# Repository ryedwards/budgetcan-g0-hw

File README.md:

# BUDGETCANFD_G0-Hardware
 BUDGETCANFD_G0-Hardware files

# HARDWARE IMAGE

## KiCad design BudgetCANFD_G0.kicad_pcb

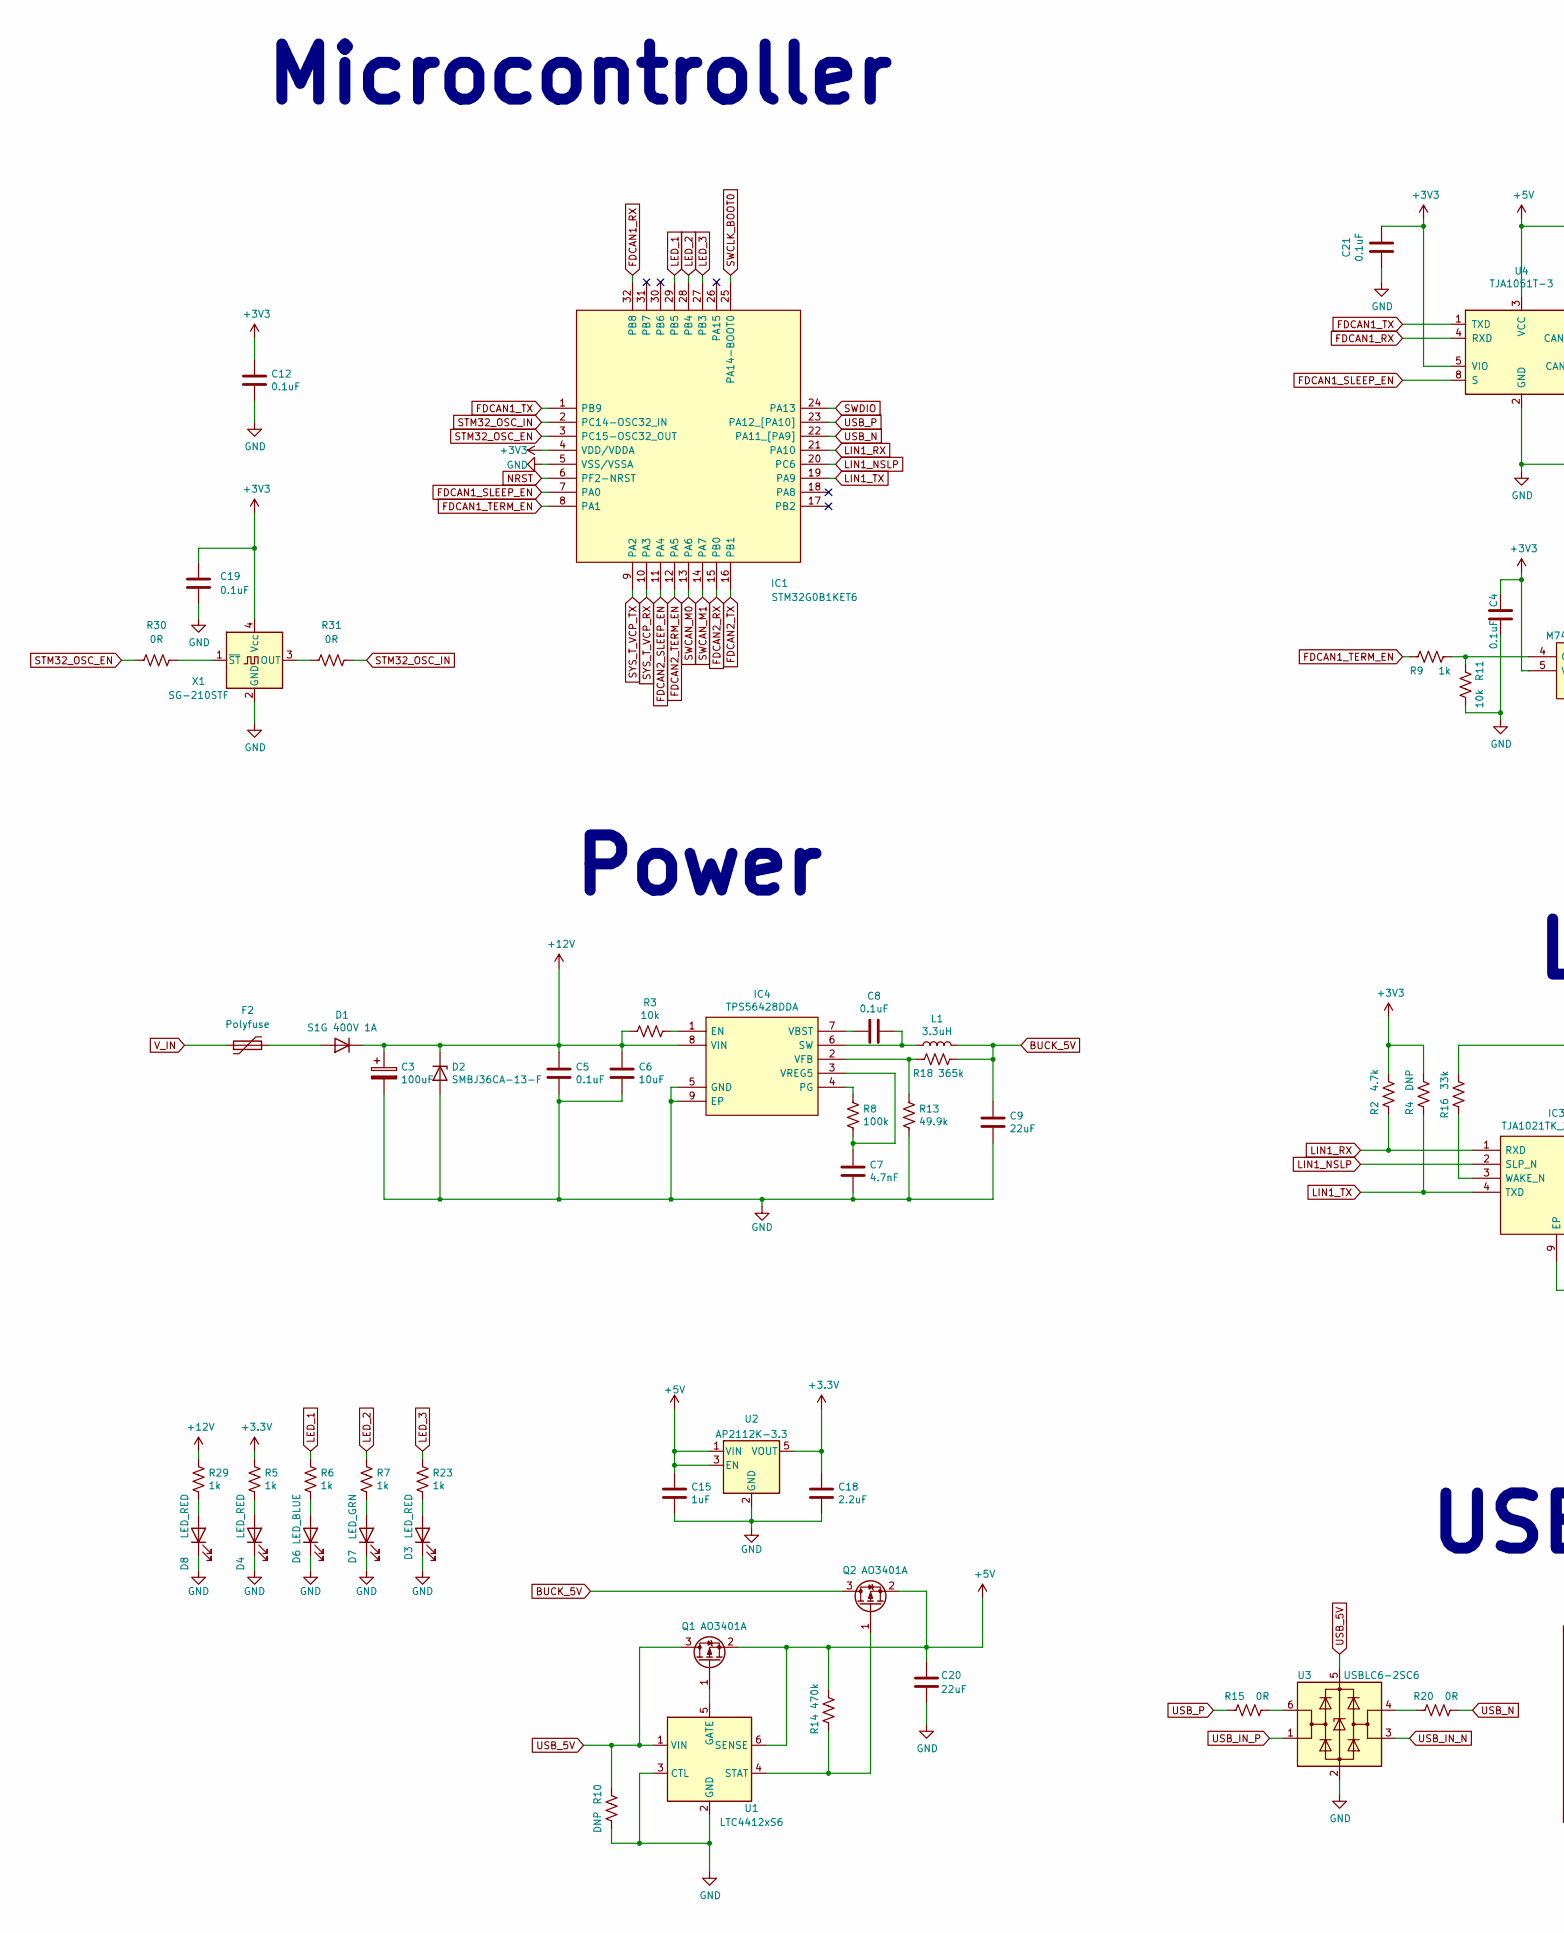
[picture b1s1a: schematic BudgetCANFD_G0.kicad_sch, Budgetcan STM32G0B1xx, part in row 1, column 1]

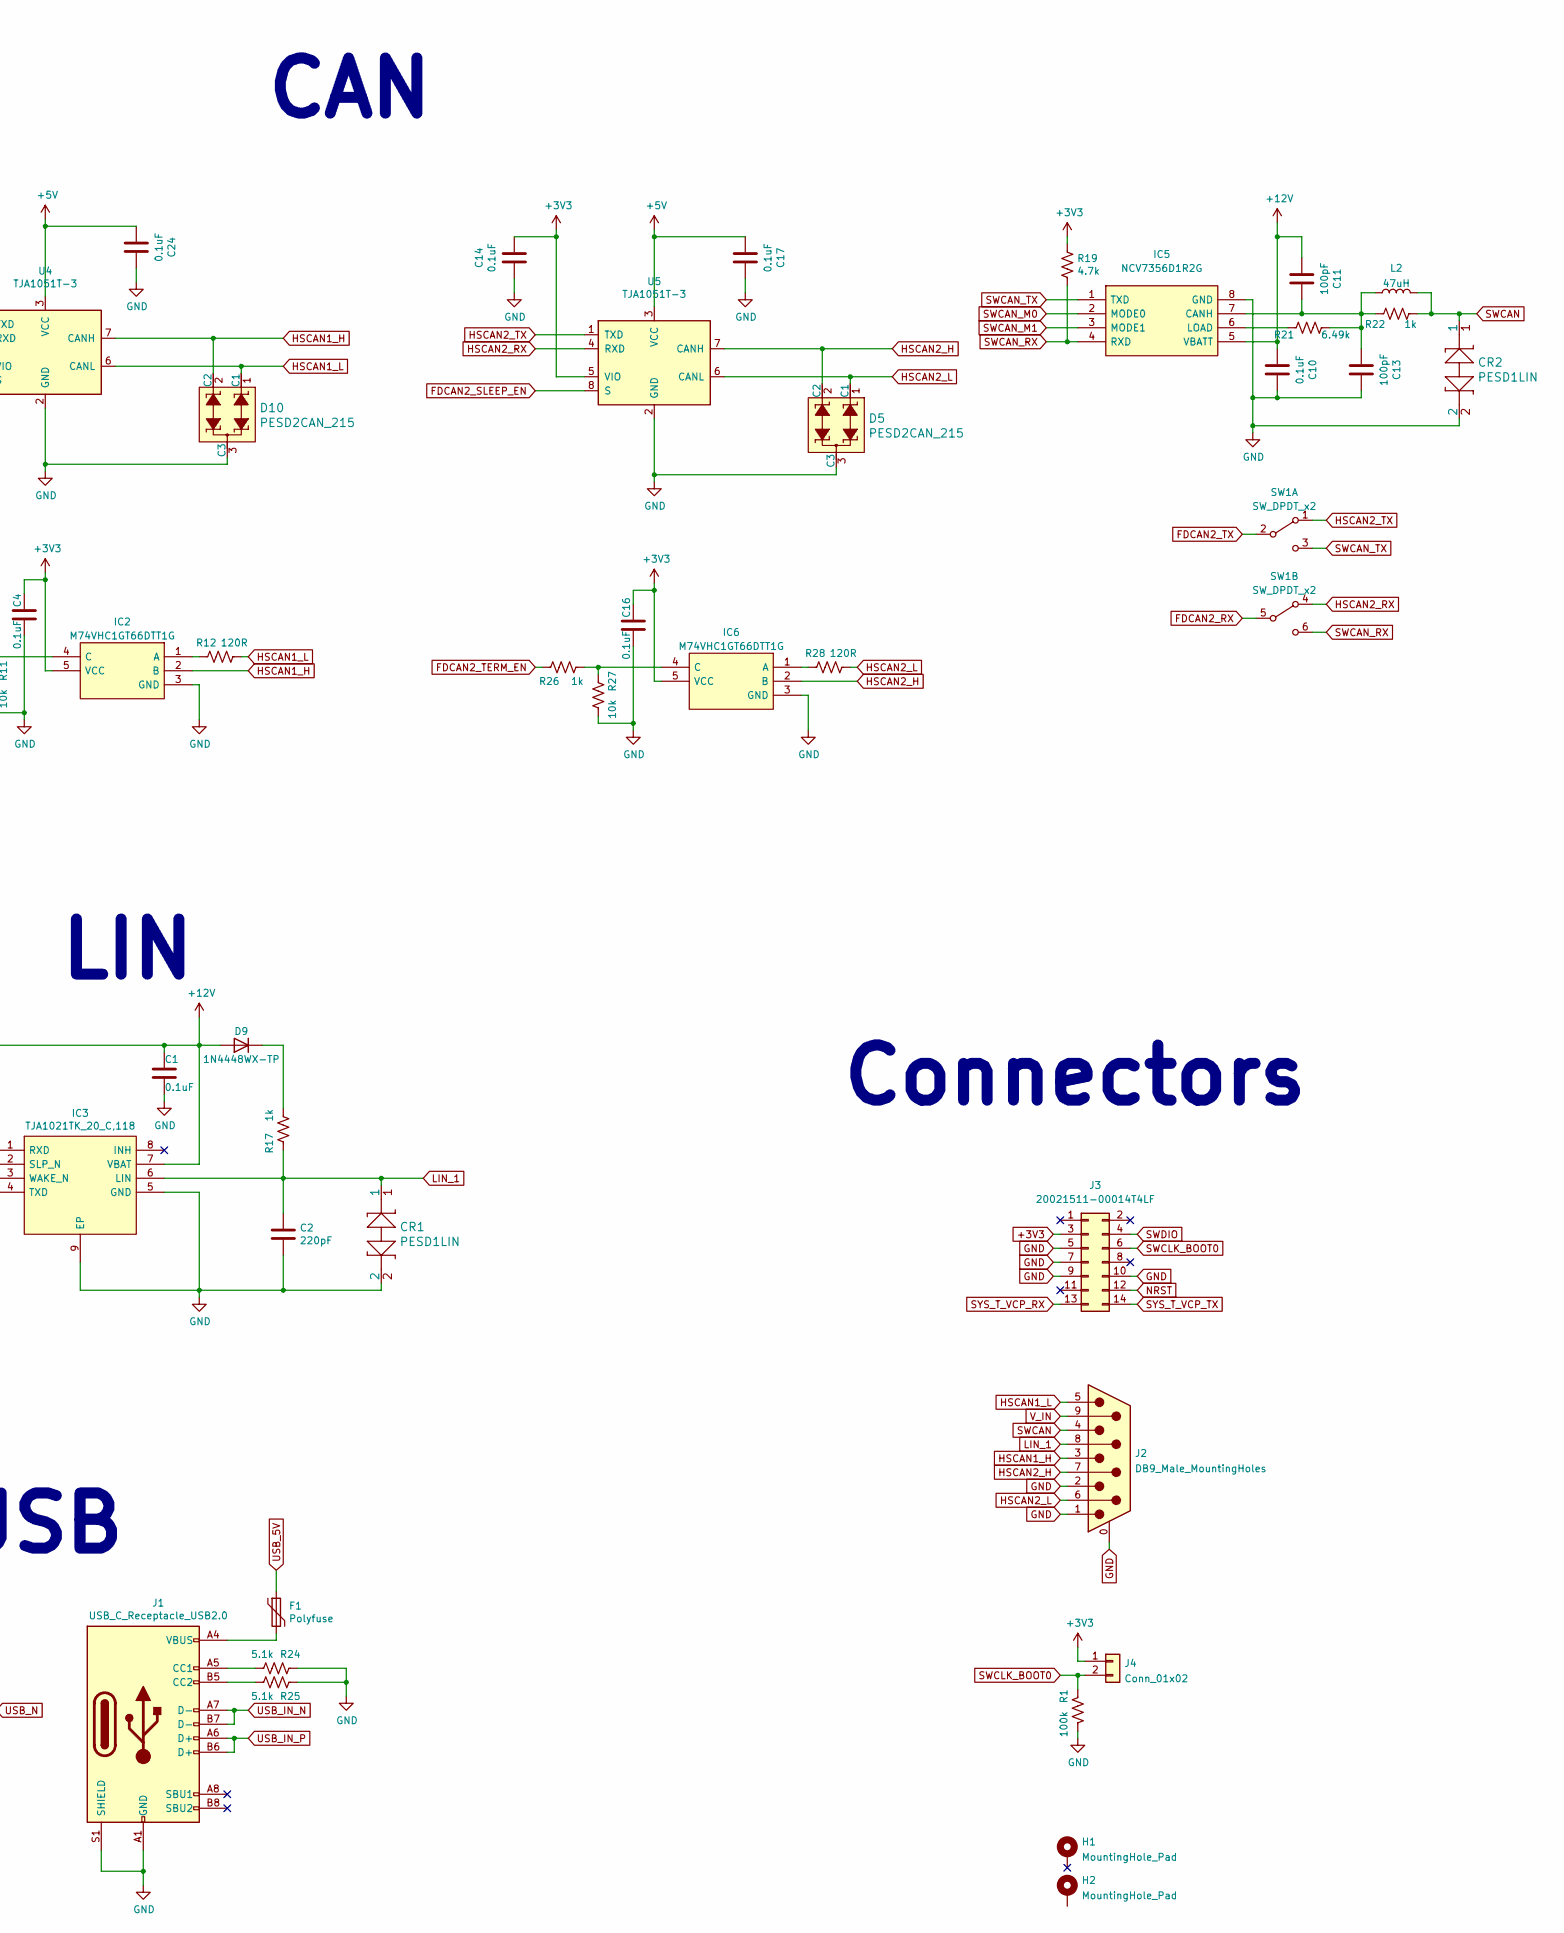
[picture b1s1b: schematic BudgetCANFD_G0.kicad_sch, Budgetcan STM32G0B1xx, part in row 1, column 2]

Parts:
C1, C4, C5, C8, C10, C12, C14, C16, C17, C21, C24: 0.1uF; C_0603_1608Metric; Manufacturer_Part_Number CC0603KRX7R8BB104; LCSC Part # C14663
C2: 220pF; C_0603_1608Metric; Manufacturer_Part_Number CC0603JRNPO9BN221; LCSC Part # C1603
C3: 100uF; CP_Elec_6.3x7.7; Manufacturer_Part_Number EMZA250ADA101MF80G; LCSC Part # C127971
C6: 10uF; C_1206_3216Metric; Manufacturer_Part_Number CL31B106KQHNFNE; LCSC Part # C13585
C7: 4.7nF; C_0603_1608Metric; Manufacturer_Part_Number CGA3E2X7R2A472K080AA; LCSC Part # C53987
C9, C20: 22uF; C_1206_3216Metric; Manufacturer_Part_Number EMK316ABJ226ML-T; LCSC Part # C90146
C11, C13: 100pF; C_0805_2012Metric; Manufacturer_Part_Number CC0603KRX7R8BB104; LCSC Part # C14663
C15: 1uF; C_0603_1608Metric; Manufacturer_Part_Number CC0603KRX7R8BB104; LCSC Part # C14663
C18: 2.2uF; C_0603_1608Metric; Manufacturer_Part_Number CC0603KRX7R8BB104; LCSC Part # C14663
C19: 0.1uF; C_0402_1005Metric; Digi-Key_PN 1276-1002-1-ND
CR1, CR2: PESD1LIN; D_SOD-323_HandSoldering; Manufacturer_Part_Number PESD1LIN,135; LCSC Part # C58901
D1: S1G 400V 1A; D_SMA; Manufacturer_Part_Number S1G; LCSC Part # C412437
D2: SMBJ36CA-13-F; D_SMB; Manufacturer_Part_Number SMBJ36CA-13-F; LCSC Part # C78421
D3, D4, D8: LED_RED; LED_0603_1608Metric; Manufacturer_Part_Number LS Q976-NR-1; LCSC Part # C2286
D5, D10: PESD2CAN_215; SOT-23; MPN PESD2CAN,215; Digi-Key_PN 1727-3891-1-ND
D6: LED_BLUE; LED_0603_1608Metric; Manufacturer_Part_Number LB Q39E-N1OO-35-1; LCSC Part # C72041
D7: LED_GRN; LED_0603_1608Metric; Manufacturer_Part_Number LG Q396-PS-35; LCSC Part # C72043
D9: ‎1N4448WX-TP‎; D_SOD-323_HandSoldering; Manufacturer_Part_Number ‎1N4448WX-TP‎; Digi-Key_PN 1N4448WXTPMSCT-ND
F1: Polyfuse; Fuse_0805_2012Metric; Manufacturer_Part_Number 0ZCK0035FF2G; LCSC Part # C369150
F2: Polyfuse; Fuse_1812_4532Metric; Manufacturer_Part_Number 0ZCG0200AF2B; Digi-Key_PN 507-2074-1-ND
H1, H2: MountingHole_Pad; MountingHole_3.2mm_M3_Pad_TopBottom
IC1: STM32G0B1KET6; LQFP-32_7x7mm_P0.8mm; Mouser Part Number 511-STM32G0B1KET6
IC2, IC6: M74VHC1GT66DTT1G; SOT-353_SC-70-5; Mouser Part Number 595-LVC1G66QDCKRQ1
IC3: TJA1021TK_20_C,118; HVSON-8-1EP_3x3mm_P0.65mm_EP1.6x2.4mm; Mouser Part Number 771-TJA1021TK20C1
IC4: TPS56428DDA; HSOP-8-1EP_3.9x4.9mm_P1.27mm_EP2.41x3.1mm_ThermalVias; Mouser Part Number 595-TPS56428DDA
IC5: NCV7356D1R2G; SOIC-8_3.9x4.9mm_P1.27mm; Manufacturer_Part_Number TH8056KDC-A8; Digi-Key_PN NCV7356D1R2GOSCT-ND
J1: USB_C_Receptacle_USB2.0; USB_C_Receptacle_GCT_USB4085; Manufacturer_Part_Number USB4085-GF-A; Digi-Key_PN 2073-USB4085-GF-ACT-ND
J2: DB9_Male_MountingHoles; DSUB-9_Male_Horizontal_P2.77x2.84mm_EdgePinOffset4.94mm_Hou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; Digi-Key_PN AE10968-ND
J3: 20021511-00014T4LF; PinHeader_2x07_P1.27mm_Vertical; Mouser Part Number 200-FTSH10701LDK
J4: Conn_01x02; PinHeader_1x02_P2.54mm_Vertical
L1: 3.3uH; L_Taiyo-Yuden_NR-50xx; LCSC Part # C167908
L2: 47uH; L_0805_2012Metric; Digi-Key_PN 490-4031-1-ND
Q1, Q2: AO3401A; SOT-23; LCSC Part # C15127
R1, R8: 100k; R_0603_1608Metric; Manufacturer_Part_Number RC0603FR-07100KL; LCSC Part # C25803
R2, R19: 4.7k; R_0603_1608Metric; Manufacturer_Part_Number RC0603JR-074K7L; LCSC Part # C23162
R3, R11, R27: 10k; R_0603_1608Metric; Manufacturer_Part_Number RC0603FR-0710KL; LCSC Part # C25804
R4: DNP; R_0603_1608Metric
R5, R6, R7, R9, R17, R23, R26, R29: 1k; R_0603_1608Metric; Manufacturer_Part_Number RC0603FR-071KL; LCSC Part # C21190
R10: DNP; R_0402_1005Metric
R12, R28: 120R; R_0603_1608Metric; Manufacturer_Part_Number RC0603FR-07120RL; LCSC Part # C22787
R13: 49.9k; R_0603_1608Metric; Manufacturer_Part_Number AF0603FR-0749K9L; LCSC Part # C23184
R14: 470k; R_0603_1608Metric; Manufacturer_Part_Number RC0603FR-07470KL; LCSC Part # C23178
R15, R20: 0R; R_0603_1608Metric; Manufacturer_Part_Number RC0603JR-070RL; LCSC Part # C21189
R16: 33k; R_0603_1608Metric; Manufacturer_Part_Number RC0603FR-0733K2L; LCSC Part # C4216
R18: 365k; R_0603_1608Metric; Manufacturer_Part_Number 13-AC0603FR-07365KLCT-ND; LCSC Part # C23031
R21: 6.49k; R_1206_3216Metric; Digi-Key_PN P6.49KFCT-ND
R22: 1k; R_1206_3216Metric; Manufacturer_Part_Number RC0603FR-071KL; LCSC Part # C21190
R24, R25: 5.1k; R_0603_1608Metric; Manufacturer_Part_Number RC0603JR-075K1L; LCSC Part # C23186
R30, R31: 0R; R_0402_1005Metric; Digi-Key_PN CR0402AJ/-000GASCT-ND
SW1: SW_DPDT_x2; SW_DPDT_CK_JS202011JCQN; Manufacturer_Part_Number JS202011JCQN; Digi-Key_PN CKN10723CT-ND
U1: LTC4412xS6; TSOT-23-6; Manufacturer_Part_Number LTC4412xS6; LCSC Part # C521306
U2: AP2112K-3.3; SOT-23-5; Manufacturer_Part_Number AP2112K-3.3; LCSC Part # C51118
U3: USBLC6-2SC6; SOT-23-6; Manufacturer_Part_Number USBLC6-2SC6; LCSC Part # C2687116
U4, U5: TJA1051T-3; SOIC-8_3.9x4.9mm_P1.27mm; LCSC Part # C38695
X1: SG-210STF; Oscillator_SMD_SeikoEpson_SG210-4Pin_2.5x2.0mm; Digi-Key_PN 50-ECS-2520MVLC-080-BN-CT-ND

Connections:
+5V: C15.1, C17.2, C20.1, C24.2, Q1.2 (S), Q2.2 (S), R14.2, U1.6 (SENSE), U2.1 (VIN), U2.3 (EN), U4.3 (VCC), U5.3 (VCC)
+12V: C1.1, C3.1, C5.1, C6.1, C10.2, C11.2, D1.1 (K), D2.1 (K), D9.2 (A), IC3.7 (VBAT), IC4.8 (VIN), IC5.5 (VBATT), R3.2, R16.2, R29.2
BUCK_5V: C9.1, L1.2, Q2.3 (D), R18.1
FDCAN1_RX: IC1.32 (PB8), U4.4 (RXD)
FDCAN1_SLEEP_EN: IC1.7 (PA0), U4.8 (S)
FDCAN1_TERM_EN: IC1.8 (PA1), R9.1
FDCAN1_TX: IC1.1 (PB9), U4.1 (TXD)
FDCAN2_RX: IC1.15 (PB0), SW1.5 (B)
FDCAN2_SLEEP_EN: IC1.11 (PA4), U5.8 (S)
FDCAN2_TERM_EN: IC1.12 (PA5), R26.1
FDCAN2_TX: IC1.16 (PB1), SW1.2 (B)
GND: C1.2, C2.2, C3.2, C4.2, C5.2, C6.2, C7.2, C9.2, C10.1, C12.2, C13.1, C14.2, C15.2, C16.2, C17.1, C18.2, C19.2, C20.2, C21.2, C24.1, CR1.2, CR2.2, D2.2 (A), D3.1 (K), D4.1 (K), D5.3 (C3), D6.1 (K), D7.1 (K), D8.1 (K), D10.3 (C3), IC1.5 (VSS/VSSA), IC2.3 (GND), IC3.5 (GND), IC3.9 (EP), IC4.5 (GND), IC4.9 (EP), IC5.8 (GND), IC6.3 (GND), J1.A1 (GND), J1.A12 (GND), J1.B1 (GND), J1.B12 (GND), J1.S1 (SHIELD), J2.0 (PAD), J2.1, J2.2, J3.5, J3.7, J3.9, J3.10, R1.2, R10.2, R11.2, R13.2, R24.1, R25.1, R27.2, U1.2 (GND), U1.3 (CTL), U2.2 (GND), U3.2 (GND), U4.2 (GND), U5.2 (GND), X1.2 (GND)
HSCAN1_H: D10.2 (C2), IC2.2 (B), J2.3, U4.7 (CANH)
HSCAN1_L: D10.1 (C1), J2.5, R12.2, U4.6 (CANL)
HSCAN2_H: D5.2 (C2), IC6.2 (B), J2.7, U5.7 (CANH)
HSCAN2_L: D5.1 (C1), J2.6, R28.2, U5.6 (CANL)
HSCAN2_RX: SW1.4 (A), U5.4 (RXD)
HSCAN2_TX: SW1.1 (A), U5.1 (TXD)
LED_1: IC1.29 (PB5), R6.2
LED_2: IC1.28 (PB4), R7.2
LED_3: IC1.27 (PB3), R23.2
LIN1_NSLP: IC1.20 (PC6), IC3.2 (SLP_N)
LIN1_RX: IC1.21 (PA10), IC3.1 (RXD), R2.1
LIN1_TX: IC1.19 (PA9), IC3.4 (TXD), R4.1
LIN_1: C2.1, CR1.1, IC3.6 (LIN), J2.8, R17.1
NRST: IC1.6 (PF2-NRST), J3.12
unnamed: C7.1, IC4.3 (VREG5), R8.2
unnamed: C8.1, IC4.6 (SW), L1.1
unnamed: C8.2, IC4.7 (VBST)
unnamed: C11.1, C13.2, IC5.7 (CANH), L2.1, R21.1, R22.2
unnamed: D1.2 (A), F2.2
unnamed: D3.2 (A), R23.1
unnamed: D4.2 (A), R5.1
unnamed: D6.2 (A), R6.1
unnamed: D7.2 (A), R7.1
unnamed: D8.2 (A), R29.1
unnamed: D9.1 (K), R17.2
unnamed: F1.2, J1.A4 (VBUS), J1.A9 (VBUS), J1.B4 (VBUS), J1.B9 (VBUS)
unnamed: IC2.1 (A), R12.1
unnamed: IC2.4 (C), R9.2, R11.1
unnamed: IC3.3 (WAKE_N), R16.1
unnamed: IC4.1 (EN), R3.1
unnamed: IC4.2 (VFB), R13.1, R18.2
unnamed: IC4.4 (PG), R8.1
unnamed: IC5.6 (LOAD), R21.2
unnamed: IC6.1 (A), R28.1
unnamed: IC6.4 (C), R26.2, R27.1
unnamed: J1.A5 (CC1), R24.2
unnamed: J1.B5 (CC2), R25.2
unnamed: Q1.1 (G), U1.5 (GATE)
unnamed: Q2.1 (G), R14.1, U1.4 (STAT)
unnamed: R15.2, U3.6 (I/O1)
unnamed: R20.1, U3.4 (I/O2)
unnamed: R30.1, X1.1 (~ST)
unnamed: R31.2, X1.3 (OUT)
STM32_OSC_EN: IC1.3 (PC15-OSC32_OUT), R30.2
STM32_OSC_IN: IC1.2 (PC14-OSC32_IN), R31.1
SWCAN: CR2.1, J2.4, L2.2, R22.1
SWCAN_M0: IC1.13 (PA6), IC5.2 (MODE0)
SWCAN_M1: IC1.14 (PA7), IC5.3 (MODE1)
SWCAN_RX: IC5.4 (RXD), R19.1, SW1.6 (C)
SWCAN_TX: IC5.1 (TXD), SW1.3 (C)
SWCLK_BOOT0: IC1.25 (PA14-BOOT0), J3.6, J4.2, R1.1
SWDIO: IC1.24 (PA13), J3.4
SYS_T_VCP_RX: IC1.10 (PA3), J3.13
SYS_T_VCP_TX: IC1.9 (PA2), J3.14
USB_5V: F1.1, Q1.3 (D), R10.1, U1.1 (VIN), U3.5 (VBUS)
USB_IN_N: J1.A7 (D-), J1.B7 (D-), U3.3 (I/O2)
USB_IN_P: J1.A6 (D+), J1.B6 (D+), U3.1 (I/O1)
USB_N: IC1.22 (PA11_[PA9]), R20.2
USB_P: IC1.23 (PA12_[PA10]), R15.1
V_IN: F2.1, J2.9

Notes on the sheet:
LIN
Microcontroller
CAN
Power
USB
Connectors

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
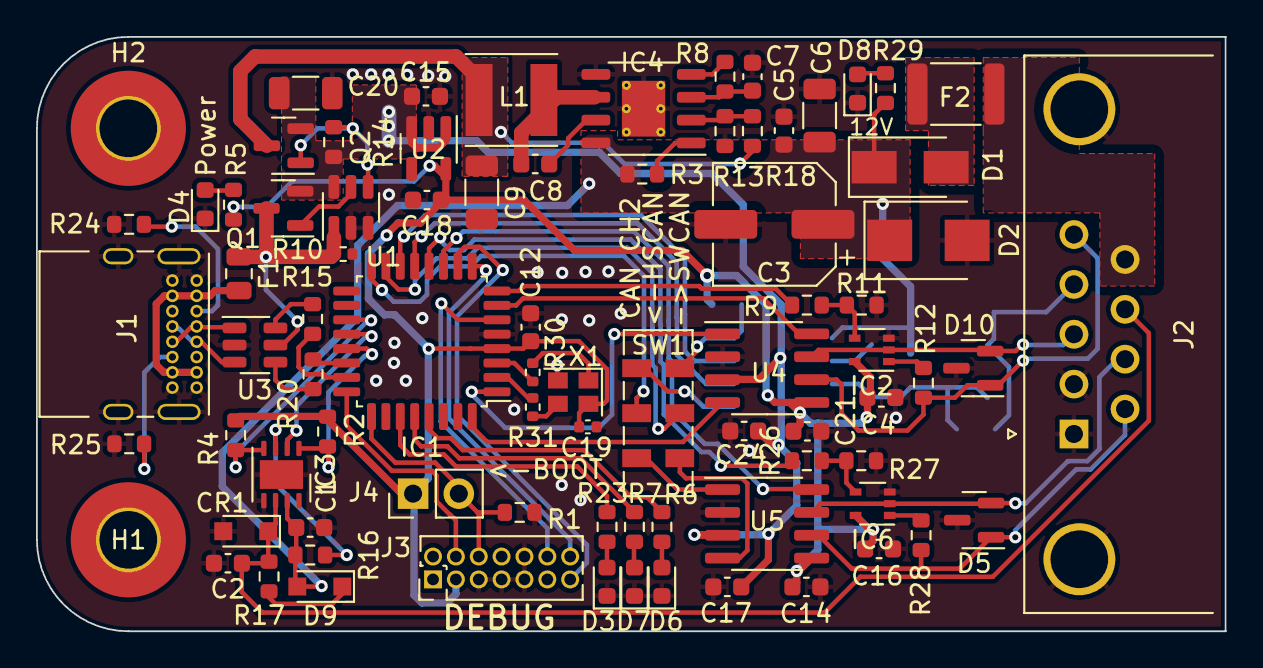
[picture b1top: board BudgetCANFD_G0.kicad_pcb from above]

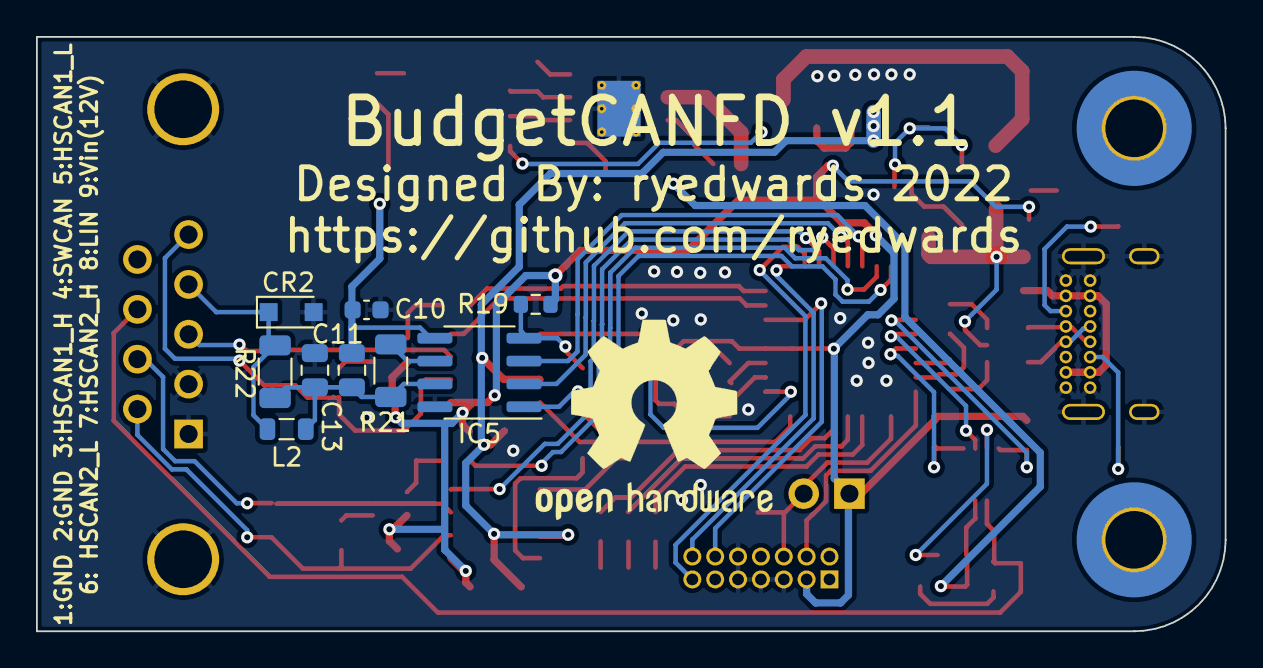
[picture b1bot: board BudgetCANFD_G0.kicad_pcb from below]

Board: 2 copper layers, 66.0 x 33.0 mm, 90 parts (9 on the bottom side), 73 nets.

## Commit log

2022-10-18 Add image
2022-11-19 Update to v1.1
    Add support for an external clock if needed in the future
2022-11-29 Update BOM
    Update part numbers for LCSC parts
2023-02-22 Add BOM and updated part numbers
